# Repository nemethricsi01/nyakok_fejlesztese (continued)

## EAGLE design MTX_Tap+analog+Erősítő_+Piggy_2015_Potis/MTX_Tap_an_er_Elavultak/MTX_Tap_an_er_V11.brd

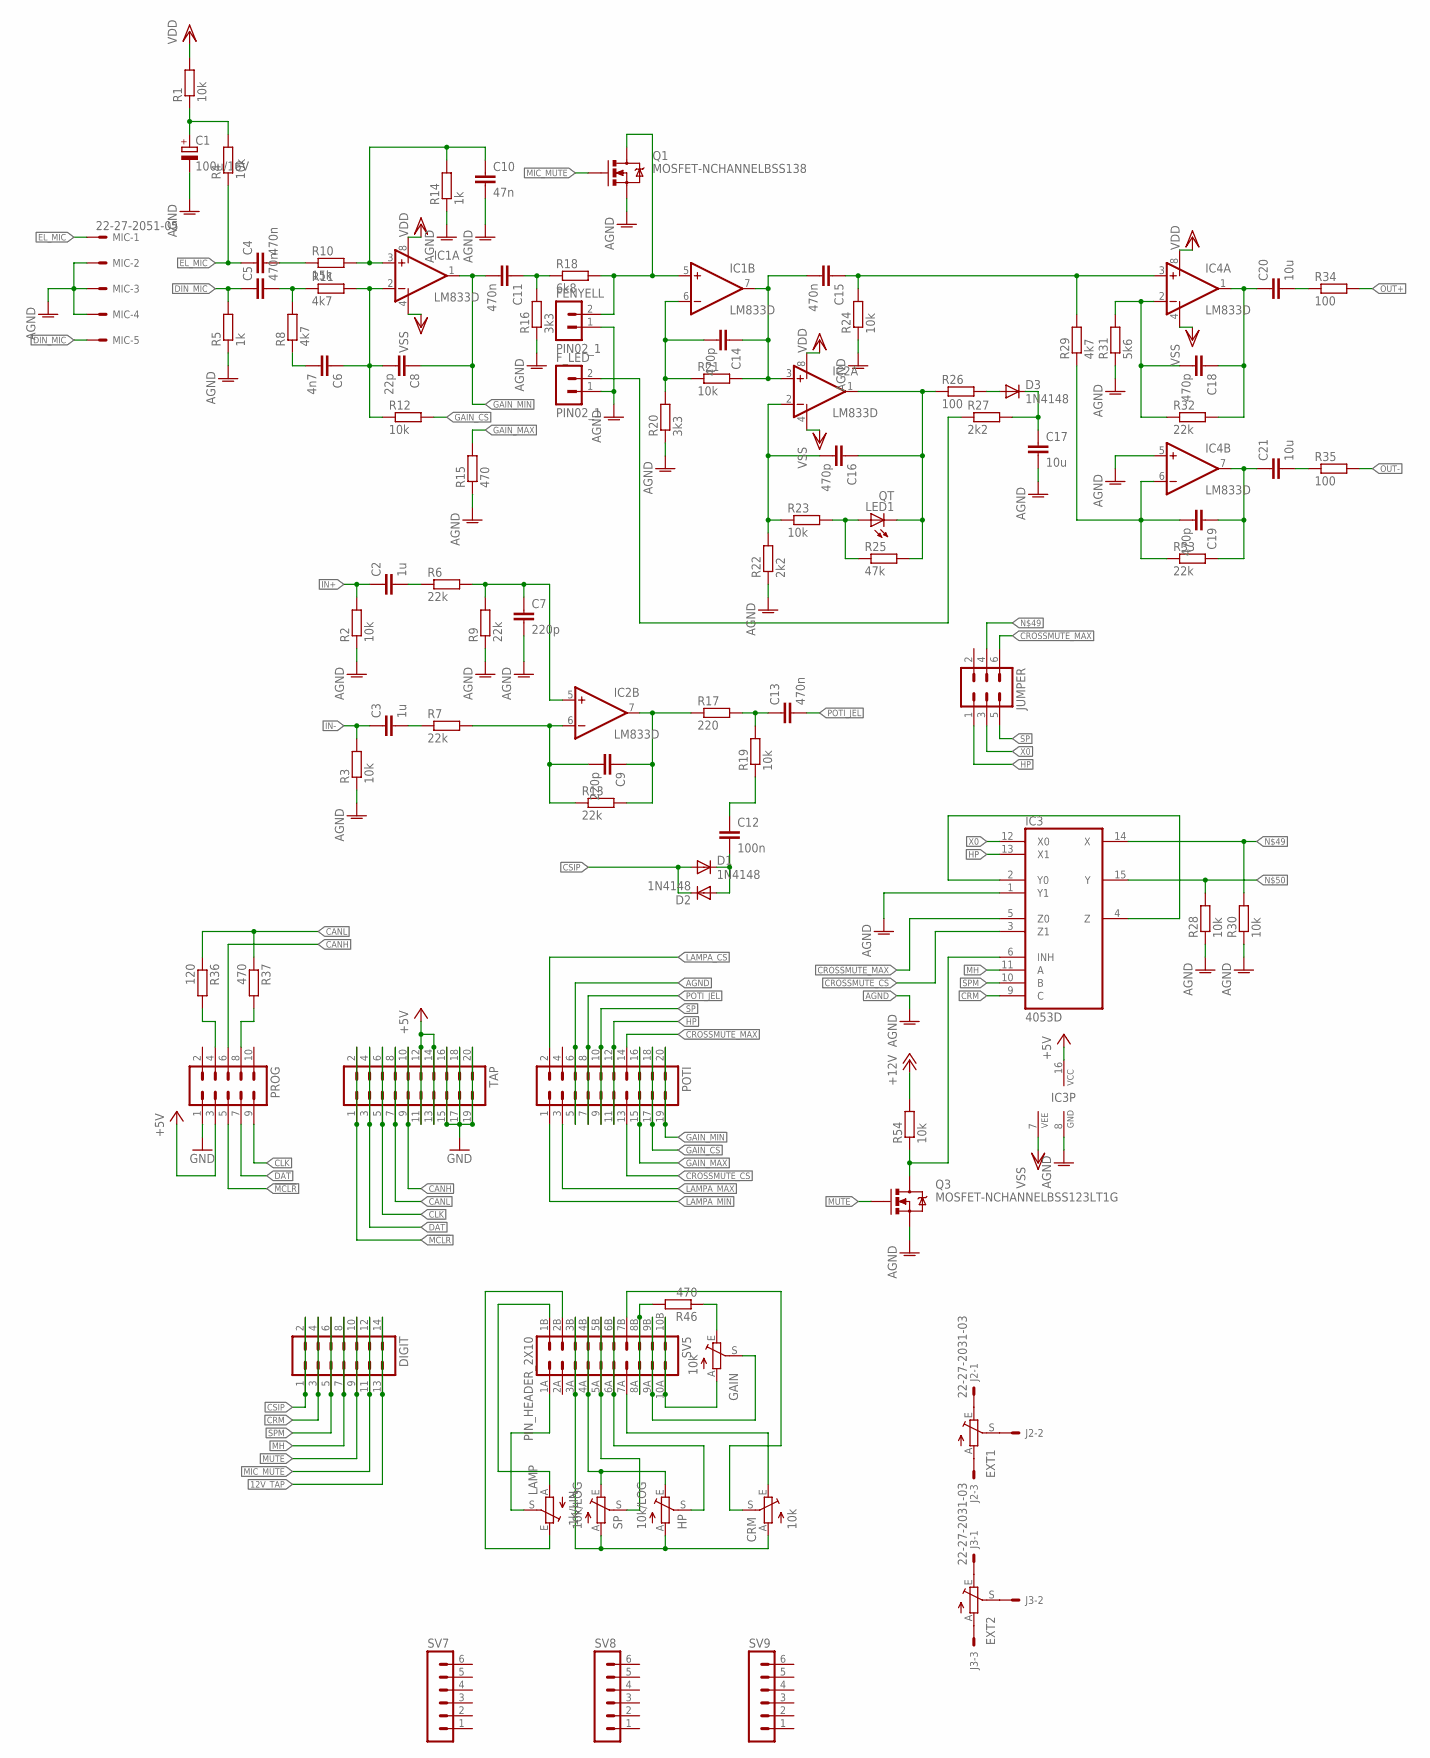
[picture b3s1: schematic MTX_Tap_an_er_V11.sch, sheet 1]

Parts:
C1: 100u/16V; E2,5-5
C2, C3: 1u; C0805
C4, C5, C11, C13, C15: 470n; C0805
C6: 4n7; C0805
C7, C9: 220p; C0805
C8: 22p; C0805
C10: 47n; C0805
C12: 100n; C0805
C14, C16, C18, C19: 470p; C0805
C17, C20, C21: 10u; C0805
CRM: 10k; PT-10
D1, D2, D3: 1N4148; SOD80C
DIGIT: MA07-2
EXT1, EXT2: TRIM_EU-PT10; PT-10
FENYELL: PIN02_1
F_LED: PIN02_1
GAIN: 10k; PT-10
HP: 10k/LOG; POT_NAR
IC1, IC2, IC4: LM833D; SO08
IC3: 4053D; SO16
J2, J3: 22-27-2031-03; 6410-03
JUMPER: MA03-2
LAMP: 1k/LIN; POT_NAR
LED1: QT; LED3MM
MIC: 22-27-2051-05; 6410-05
POTI: MA10-2
PROG: ML10L
Q1: MOSFET-NCHANNELBSS138; SOT23
Q3: MOSFET-NCHANNELBSS123LT1G; SOT23
R1, R2, R3, R4, R12, R19, R21, R23, R24, R28, R30, R54: 10k; R0805
R5, R14: 1k; R0805
R6, R7, R9, R13, R32, R33: 22k; R0805
R8, R11, R29: 4k7; R0805
R10: 15k; R0805
R15, R37, R46: 470; R0805
R16, R20: 3k3; R0805
R17: 220; R0805
R18: 6k8; R0805
R22, R27: 2k2; R0805
R25: 47k; R0805
R26, R34, R35: 100; R0805
R31: 5k6; R0805
R36: 120; R0805
SP: 10k/LOG; POT_NAR
SV5: PIN_HEADER_2X10; PIN_HEADER_2X10SMD
SV7, SV8, SV9: MA06-1
TAP: MA10-2

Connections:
1.: C9.1, IC2.7 (OUT), R13.2, R17.1
12V_TAP: DIGIT.13, DIGIT.14; also elsewhere on the board
!MCLR: PROG.5, TAP.1, TAP.2
+5V: IC3.16 (VCC), PROG.3, TAP.11, TAP.12, TAP.13, TAP.14; also elsewhere on the board
+12V: R54.2; also elsewhere on the board
AGND: C1.-, C7.2, C10.2, C17.2, FENYELL.1, F_LED.1, IC3.1 (Y1), IC3.8 (GND), IC4.5 (+IN), MIC.2, MIC.3, MIC.4, POTI.5, POTI.6, Q1.2 (S), Q3.2 (S), R2.1, R3.1, R5.1, R9.1, R14.1, R15.1, R16.1, R20.1, R22.1, R24.1, R28.1, R30.1, R31.1; also elsewhere on the board
CANH: PROG.6, TAP.9, TAP.10; also elsewhere on the board
CANL: R36.1, R37.1, TAP.7, TAP.8; also elsewhere on the board
CLK: PROG.9, TAP.5, TAP.6
CRM: DIGIT.3, DIGIT.4, IC3.9 (C)
CROSSMUTE_CS: IC3.3 (Z1), POTI.13
CROSSMUTE_MAX: IC3.5 (Z0), JUMPER.6, POTI.14
CSIP: D1.A, D2.C, DIGIT.1, DIGIT.2
DAT: PROG.7, TAP.3, TAP.4
DIN_MIC: C5.1, MIC.5, R5.2
EL_MIC: C4.1, MIC.1, R4.1
GAIN_CS: POTI.17, POTI.18, R12.2
GAIN_MAX: POTI.15, POTI.16, R15.2
GAIN_MIN: C8.1, C11.2, IC1.1 (OUT), POTI.19, POTI.20
GND: PROG.1, TAP.15, TAP.16, TAP.17, TAP.18, TAP.19, TAP.20; also elsewhere on the board
HP: IC3.13 (X1), JUMPER.1, POTI.11, POTI.12
IN+: C2.1, R2.2; also elsewhere on the board
IN-: C3.1, R3.2; also elsewhere on the board
LAMPA_CS: POTI.2; also elsewhere on the board
LAMPA_MAX: POTI.3; also elsewhere on the board
LAMPA_MIN: POTI.1; also elsewhere on the board
MH: DIGIT.7, DIGIT.8, IC3.11 (A)
MIC_MUTE: DIGIT.11, DIGIT.12, Q1.1 (G)
MUTE: DIGIT.9, DIGIT.10, Q3.1 (G)
unnamed: C1.+, R1.1, R4.2
unnamed: C4.2, R10.1
unnamed: C5.2, R8.2, R11.1
unnamed: C10.1, IC1.3 (+IN), R10.2, R14.2
unnamed: C6.1, C8.2, IC1.2 (-IN), R11.2, R12.1
unnamed: C6.2, R8.1
unnamed: FENYELL.2, IC1.5 (+IN), Q1.3 (D), R18.2
unnamed: CRM.E, SV5.7A (13)
unnamed: CRM.A, HP.A, SP.A, SV5.3A (5), SV5.3B (6)
unnamed: IC3.2 (Y0), IC3.4 (Z)
unnamed: C11.1, R16.2, R18.1
unnamed: C18.2, IC4.2 (-IN), R31.2, R32.1
unnamed: C18.1, C20.1, IC4.1 (OUT), R32.2
unnamed: C14.2, IC1.6 (-IN), R20.2, R21.1
unnamed: C14.1, C15.2, IC1.7 (OUT), IC2.3 (+IN), R21.2
unnamed: C16.2, IC2.2 (-IN), R22.2, R23.1
unnamed: C19.2, IC4.6 (-IN), R29.1, R33.1
unnamed: LED1.A, R23.2, R25.1
unnamed: C16.1, IC2.1 (OUT), LED1.K (C), R25.2, R26.1
unnamed: D3.A, R26.2
unnamed: C17.1, D3.C, R27.2
unnamed: F_LED.2, R27.1
unnamed: C15.1, IC4.3 (+IN), R24.2, R29.2
unnamed: C19.1, C21.1, IC4.7 (OUT), R33.2
unnamed: C21.2, R35.1
unnamed: C20.2, R34.1
unnamed: C2.2, R6.1
unnamed: HP.E, SP.E, SV5.4A (7), SV5.4B (8)
unnamed: C7.1, IC2.5 (+IN), R6.2, R9.2
unnamed: C3.2, R7.1
unnamed: SP.S, SV5.5A (9), SV5.5B (10)
unnamed: C12.2, D1.C, D2.A
unnamed: C9.2, IC2.6 (-IN), R7.2, R13.1
unnamed: EXT1.S, J2.2
unnamed: EXT2.S, J3.2
unnamed: C13.1, R17.2, R19.2
unnamed: C12.1, R19.1
unnamed: EXT1.E, J2.1
unnamed: EXT1.A, J2.3
unnamed: LAMP.S, SV5.1A (1)
unnamed: EXT2.A, J3.3
unnamed: EXT2.E, J3.1
unnamed: LAMP.E, SV5.2B (4)
unnamed: HP.S, SV5.6A (11), SV5.6B (12)
unnamed 81: IC3.14 (X), JUMPER.4, R30.2; also elsewhere on the board
unnamed 82: IC3.15 (Y), R28.2; also elsewhere on the board
unnamed: PROG.8, R37.2
unnamed: LAMP.A, SV5.1B (2)
unnamed: PROG.4, R36.2
unnamed: CRM.S, SV5.7B (14)
unnamed: IC3.6 (INH), Q3.3 (D), R54.1
unnamed: R46.2, SV5.8A (15), SV5.8B (16)
unnamed: GAIN.S, SV5.9A (17), SV5.9B (18)
unnamed: GAIN.A, SV5.10A (19), SV5.10B (20)
unnamed: GAIN.E, R46.1
OUT+: R34.2; also elsewhere on the board
OUT-: R35.2; also elsewhere on the board
POTI_JEL: C13.2, POTI.7, POTI.8
SP: JUMPER.5, POTI.9, POTI.10
SPM: DIGIT.5, DIGIT.6, IC3.10 (B)
VDD: IC1.8 (V+), IC2.8 (V+), IC4.8 (V+), R1.2; also elsewhere on the board
VSS: IC1.4 (V-), IC2.4 (V-), IC3.7 (VEE), IC4.4 (V-); also elsewhere on the board
X0: IC3.12 (X0), JUMPER.3

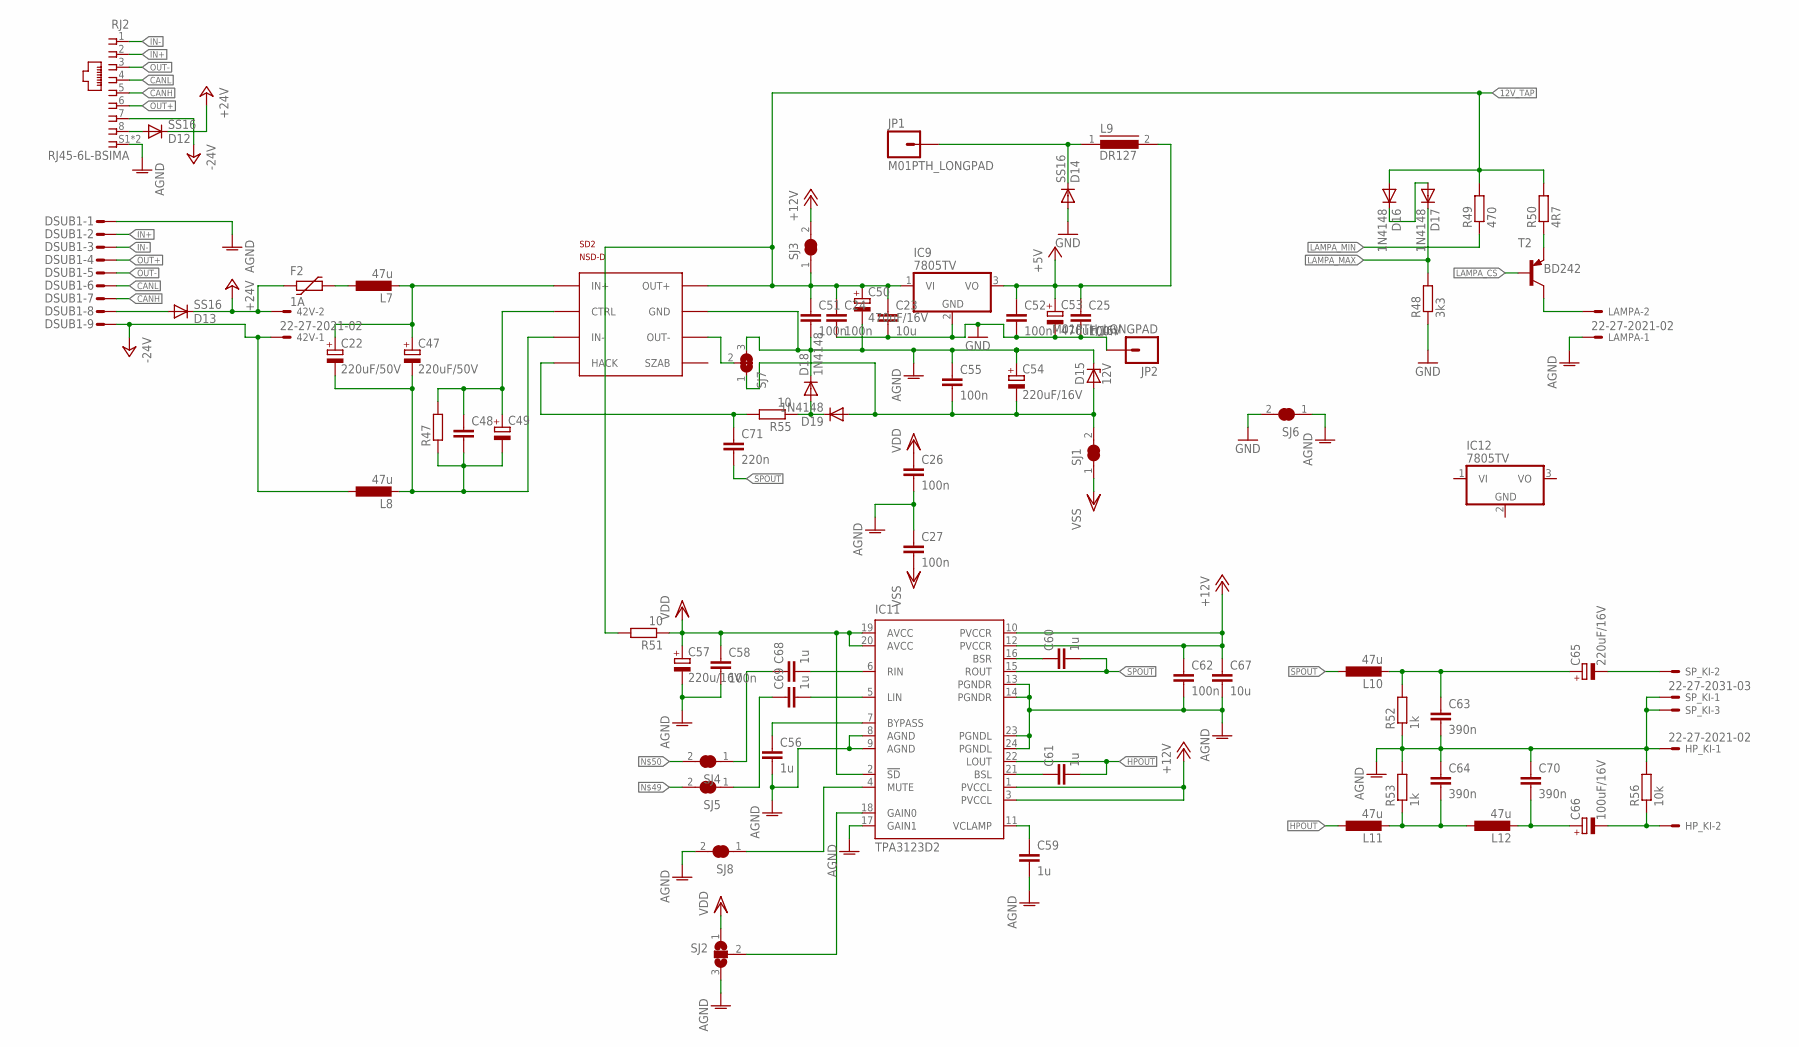
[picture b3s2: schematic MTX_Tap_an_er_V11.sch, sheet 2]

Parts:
42V: 22-27-2021-02; 6410-02
C22, C47: 220uF/50V; E3,5-8
C23, C67: 10u; C0805
C24, C25, C26, C27, C51, C52, C55, C58, C62: 100n; C0805
C48: C-EUC0805; C0805
C49: CPOL-EUE2.5-5; E2,5-5
C50, C53: 470uF/16V; E3,5-8
C54, C65: 220uF/16V; E2,5-7
C56, C59, C60, C61, C68, C69: 1u; C0805
C57: 220u/16V; E2,5-7
C63, C64, C70: 390n; C0805
C66: 100uF/16V; E2,5-6
C71: 220n; C0805
D12, D13, D14: SS16; DO-214AC
D15: 12V; SOD80C
D16, D17, D18, D19: 1N4148; SOD80C
DSUB1: M09-182S; 182-009-MALE
F2: 1A; PTC1812L
HP_KI: 22-27-2021-02; 6410-02
IC9, IC12: 7805TV; TO220V
IC11: TPA3123D2; PWP-TSSOP24
JP1, JP2: M01PTH_LONGPAD; 1X01_LONGPAD
L7, L8, L10, L11, L12: 47u; PIS2816
L9: DR127
LAMPA: 22-27-2021-02; 6410-02
R47: R-EU_R0805; R0805
R48: 3k3; R0805
R49: 470; R0805
R50: 4R7; R0805
R51: 10; R1210
R52, R53: 1k; R0805
R55: 10; R0805
R56: 10k; R0805
RJ2: RJ45-6L-BSIMA; RJ45
SD2: NSD-D
SJ1, SJ3, SJ4, SJ5, SJ6, SJ8: SOLDERJUMPER_CLOSED; SOLDERJUMPER_CLOSEDWIRE
SJ2: SJ2W; SJ_2
SJ7: SOLDERJUMPER_2WAY; SOLDERJUMPER_2WAY_OPEN_NOPASTE
SP_KI: 22-27-2031-03; 6410-03
T2: BD242; TO220V

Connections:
12V_TAP: C23.1, C24.1, C50.+, C51.1, D16.A, IC9.1 (VI), R49.2, R50.2, R51.2, SD2.OUT+, SJ3.1; also elsewhere on the board
+5V: C25.1, C52.1, C53.+, IC9.3 (VO), L9.2; also elsewhere on the board
+12V: C62.1, C67.1, IC11.1 (PVCCL), IC11.3 (PVCCL), IC11.10 (PVCCR), IC11.12 (PVCCR), SJ3.2; also elsewhere on the board
+24V: 42V.2, D12.1 (C), D13.1 (C), F2.1
-24V: 42V.1, DSUB1.9, L8.1, RJ2.7
AGND: C26.2, C27.1, C50.-, C51.2, C54.+, C55.1, C56.2, C57.-, C58.2, C59.2, C62.2, C63.2, C64.1, C67.2, C70.1, D15.C, D18.C, DSUB1.1, HP_KI.1, IC11.8 (AGND), IC11.9 (AGND), IC11.13 (PGNDR), IC11.14 (PGNDR), IC11.17 (GAIN1), IC11.23 (PGNDL), IC11.24 (PGNDL), LAMPA.1, R52.1, R53.2, R56.2, RJ2.S1 (S), RJ2.S2 (S), SD2.COMMON (GND), SJ2.3, SJ6.1, SJ7.3, SJ8.2, SP_KI.1, SP_KI.3; also elsewhere on the board
CANH: DSUB1.7, RJ2.5; also elsewhere on the board
CANL: DSUB1.6, RJ2.4; also elsewhere on the board
GND: C23.2, C24.2, C25.2, C52.2, C53.-, D14.2 (A), IC9.2 (GND), JP2.1, R48.1, SJ6.2; also elsewhere on the board
HPIN_X: C69.1, SJ5.1
HPOUT: C61.2, IC11.22 (LOUT), L11.1
IN+: DSUB1.2, RJ2.2; also elsewhere on the board
IN-: DSUB1.3, RJ2.1; also elsewhere on the board
LAMPA_CS: T2.1 (B); also elsewhere on the board
LAMPA_MAX: D17.C, R48.2; also elsewhere on the board
LAMPA_MIN: R49.1; also elsewhere on the board
unnamed: C54.-, C55.2, D15.A, D19.A, SJ1.2, SJ7.1
unnamed: D12.2 (A), RJ2.8
unnamed: C65.-, SP_KI.2
unnamed: SD2.OUT-, SJ7.2
unnamed 81: SJ5.2; also elsewhere on the board
unnamed 82: SJ4.2; also elsewhere on the board
unnamed: C71.1, R55.2, SD2.HACK
unnamed: D13.2 (A), DSUB1.8
unnamed: F2.2, L7.1
unnamed: C22.+, C47.+, L7.2, SD2.INPUT+ (IN+)
unnamed: C48.1, C49.+, R47.2, SD2.CONTROL (CTRL)
unnamed: C22.-, C47.-, C48.2, C49.-, L8.2, R47.1, SD2.INPUT- (IN-)
unnamed: D14.1 (C), JP1.1, L9.1
unnamed: R50.1, T2.3 (E)
unnamed: D16.C, D17.A
unnamed: LAMPA.2, T2.2 (C)
unnamed: C56.1, IC11.7 (BYPASS)
unnamed: C59.1, IC11.11 (VCLAMP)
unnamed: C61.1, IC11.21 (BSL)
unnamed: C60.1, IC11.16 (BSR)
unnamed: C63.1, C65.+, L10.2, R52.2
unnamed: C64.2, L11.2, L12.1, R53.1
unnamed: C66.-, HP_KI.2, R56.1
unnamed: C68.2, IC11.6 (RIN)
unnamed: C69.2, IC11.5 (LIN)
unnamed: IC11.18 (GAIN0), SJ2.2
unnamed: IC11.4 (MUTE), SJ8.1
unnamed: D18.A, D19.C, R55.1
unnamed: C66.+, C70.2, L12.2
OUT+: DSUB1.4, RJ2.6; also elsewhere on the board
OUT-: DSUB1.5, RJ2.3; also elsewhere on the board
SPIN_X: C68.1, SJ4.1
SPOUT: C60.2, C71.2, IC11.15 (ROUT), L10.1
VDD: C26.1, C57.+, C58.1, IC11.2 (!SD), IC11.19 (AVCC), IC11.20 (AVCC), R51.1, SJ2.1; also elsewhere on the board
VSS: C27.2, SJ1.1; also elsewhere on the board

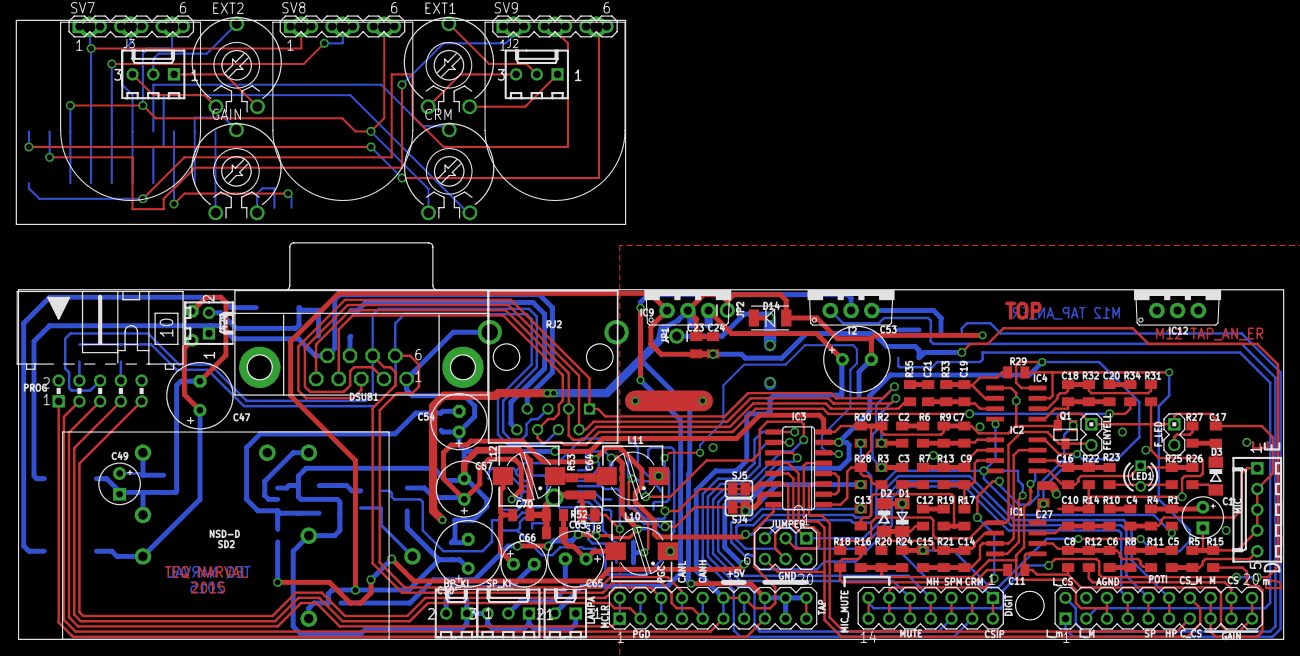
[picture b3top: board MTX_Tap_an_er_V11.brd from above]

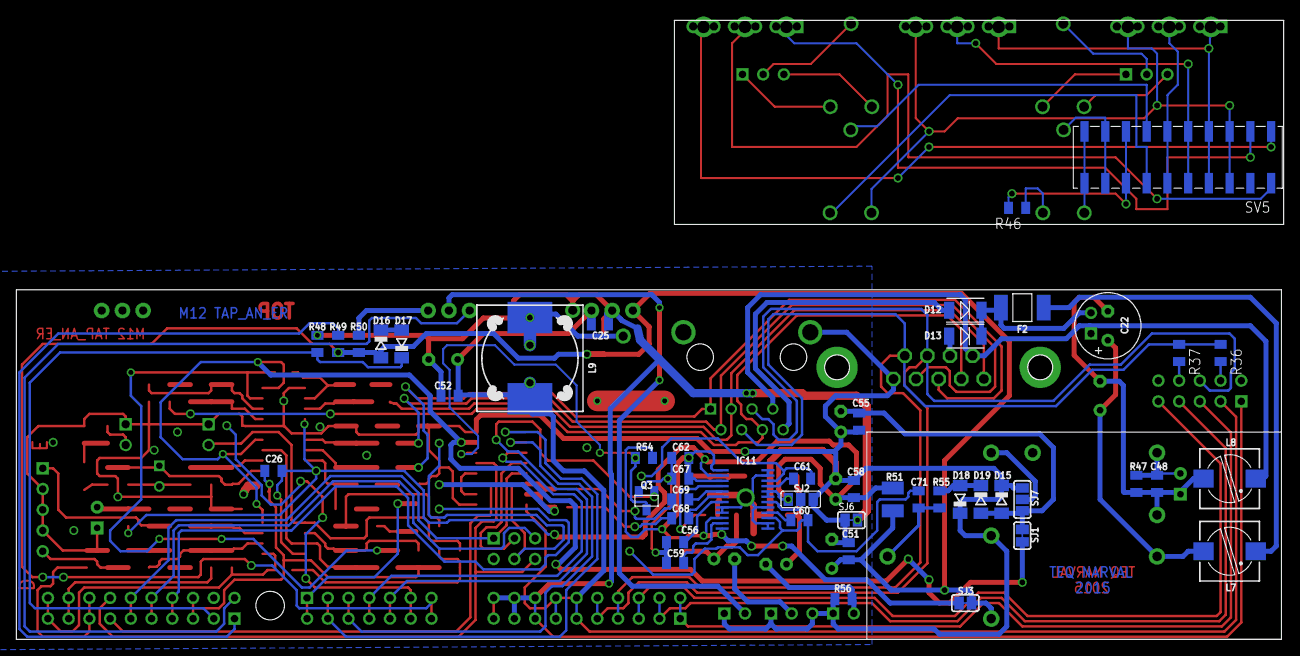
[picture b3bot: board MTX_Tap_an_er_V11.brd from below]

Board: 2 copper layers, 155.0 x 42.8 mm, 167 parts (47 on the bottom side), 125 nets.

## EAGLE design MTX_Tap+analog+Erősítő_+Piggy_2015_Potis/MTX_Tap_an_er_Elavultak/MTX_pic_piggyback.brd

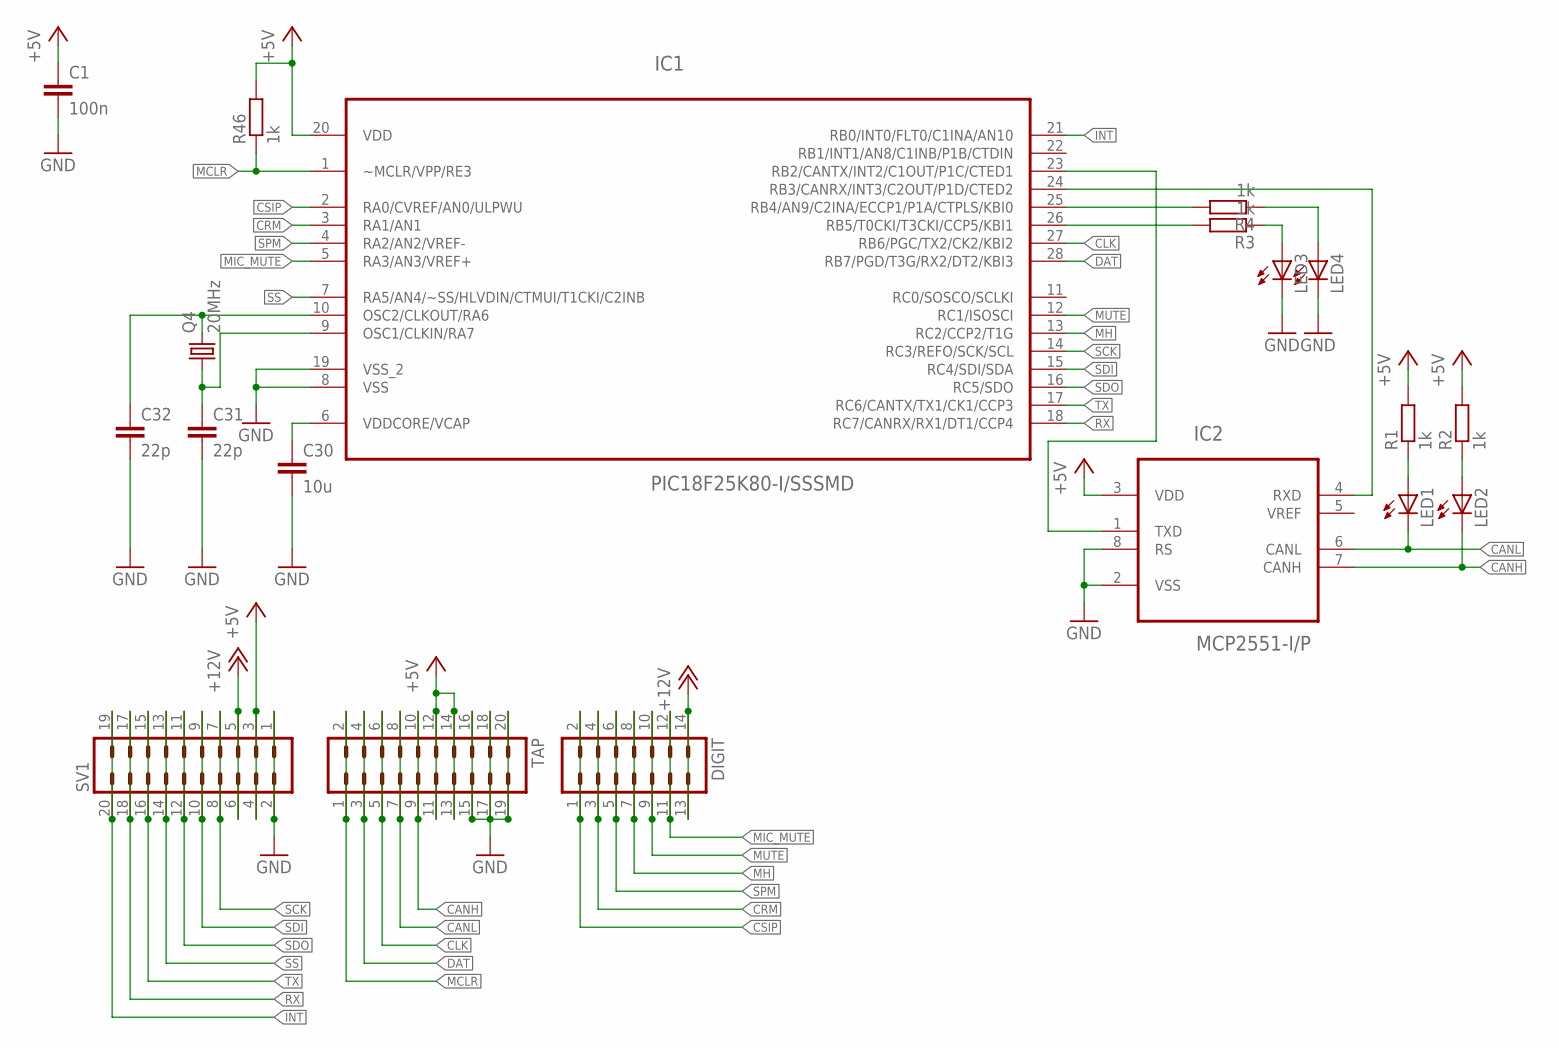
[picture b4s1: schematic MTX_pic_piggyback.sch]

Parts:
C1: 100n; C0805
C30: 10u; C0805
C31, C32: 22p; C0805
DIGIT: MA07-2
IC1: PIC18F25K80-I/SSSMD; SOP65P780X200-28N
IC2: MCP2551-I/P; DIP254P762X432-8
LED1, LED2, LED3, LED4: LEDCHIP-LED0805; CHIP-LED0805
Q4: 20MHz; HC49UP
R1, R2, R3, R4, R46: 1k; R0805
SV1: MA10-2
TAP: MA10-2

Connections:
+5V: C1.1, IC1.20 (VDD), IC2.3 (VDD), R1.2, R2.2, R46.2, SV1.3, SV1.4, TAP.11, TAP.12, TAP.13, TAP.14
+12V: DIGIT.13, DIGIT.14, SV1.5, SV1.6
CANH: IC2.7 (CANH), LED2.C, TAP.9, TAP.10
CANL: IC2.6 (CANL), LED1.C, TAP.7, TAP.8
CLK: IC1.27 (RB6/PGC/TX2/CK2/KBI2), TAP.5, TAP.6
CRM: DIGIT.3, DIGIT.4, IC1.3 (RA1/AN1)
CSIP: DIGIT.1, DIGIT.2, IC1.2 (RA0/CVREF/AN0/ULPWU)
DAT: IC1.28 (RB7/PGD/T3G/RX2/DT2/KBI3), TAP.3, TAP.4
GND: C1.2, C30.2, C31.2, C32.2, IC1.8 (VSS), IC1.19 (VSS_2), IC2.2 (VSS), IC2.8 (RS), LED3.C, LED4.C, SV1.1, SV1.2, TAP.15, TAP.16, TAP.17, TAP.18, TAP.19, TAP.20
INT: IC1.21 (RB0/INT0/FLT0/C1INA/AN10), SV1.19, SV1.20
MCLR: IC1.1 (~MCLR/VPP/RE3), R46.1, TAP.1, TAP.2
MH: DIGIT.7, DIGIT.8, IC1.13 (RC2/CCP2/T1G)
MIC_MUTE: DIGIT.11, DIGIT.12, IC1.5 (RA3/AN3/VREF+)
MUTE: DIGIT.9, DIGIT.10, IC1.12 (RC1/ISOSCI)
unnamed: LED1.A, R1.1
unnamed: LED2.A, R2.1
unnamed: LED3.A, R3.1
unnamed: IC1.26 (RB5/T0CKI/T3CKI/CCP5/KBI1), R3.2
unnamed: LED4.A, R4.1
unnamed: IC1.25 (RB4/AN9/C2INA/ECCP1/P1A/CTPLS/KBI0), R4.2
unnamed: C30.1, IC1.6 (VDDCORE/VCAP)
unnamed: C31.1, IC1.9 (OSC1/CLKIN/RA7), Q4.1
unnamed: C32.1, IC1.10 (OSC2/CLKOUT/RA6), Q4.2
unnamed: IC1.24 (RB3/CANRX/INT3/C2OUT/P1D/CTED2), IC2.4 (RXD)
unnamed: IC1.23 (RB2/CANTX/INT2/C1OUT/P1C/CTED1), IC2.1 (TXD)
RX: IC1.18 (RC7/CANRX/RX1/DT1/CCP4), SV1.17, SV1.18
SCK: IC1.14 (RC3/REFO/SCK/SCL), SV1.7, SV1.8
SDI: IC1.15 (RC4/SDI/SDA), SV1.9, SV1.10
SDO: IC1.16 (RC5/SDO), SV1.11, SV1.12
SPM: DIGIT.5, DIGIT.6, IC1.4 (RA2/AN2/VREF-)
SS: IC1.7 (RA5/AN4/~SS/HLVDIN/CTMUI/T1CKI/C2INB), SV1.13, SV1.14
TX: IC1.17 (RC6/CANTX/TX1/CK1/CCP3), SV1.15, SV1.16

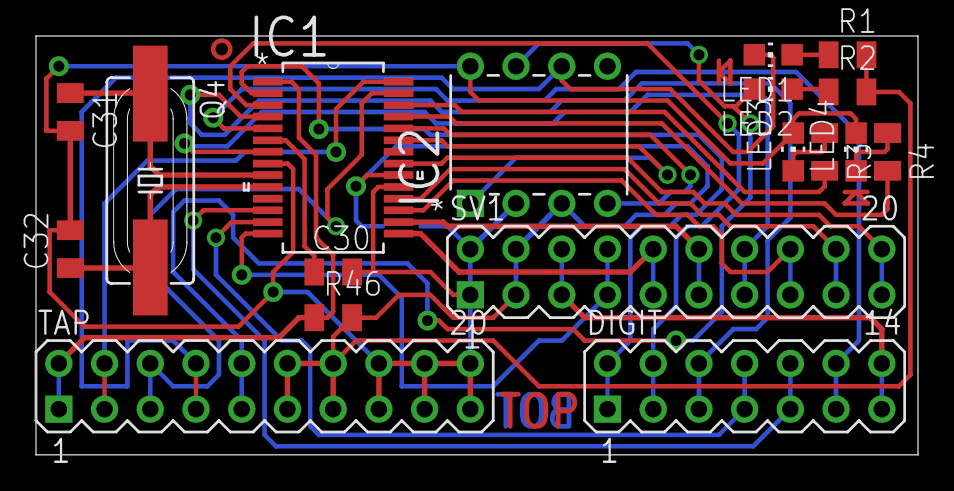
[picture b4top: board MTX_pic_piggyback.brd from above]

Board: 2 copper layers, 49.0 x 23.3 mm, 19 parts (1 on the bottom side), 32 nets.

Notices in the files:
parts and their libraries:
SparkFun-DiscreteSemi: Licensing: Creative Commons ShareAlike 4.0 International - https://creativecommons.org/licenses/by-sa/4.0
microbuilder: This work is placed in the public domain, and may be freely used for commercial and non-commercial work with the following conditions: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
